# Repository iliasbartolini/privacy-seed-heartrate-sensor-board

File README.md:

# Privacy Seed - Heart rate sensor board

KiCAD custom heart rate board based on MAX30101 to connect to a [Arduino Nano shield](https://github.com/iliasbartolini/privacy-seed-heartrate-sensor-nano-shield).
This component is part of the [Privacy Seed](https://privacy-seed.org/) project.

## Schema

## PCB

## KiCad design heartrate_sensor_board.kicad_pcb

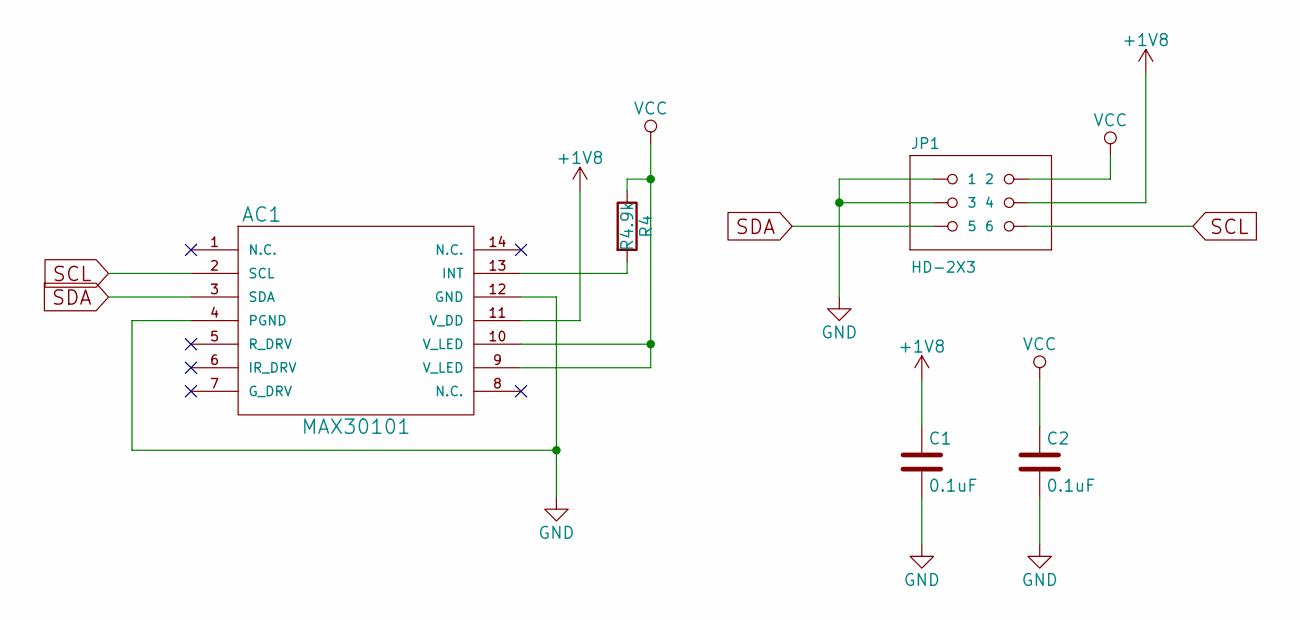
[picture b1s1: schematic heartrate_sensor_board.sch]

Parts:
AC1: MAX30101; fab-OESIP14
C1, C2: 0.1uF; fab-C1206FAB
JP1: HD-2X3; fab-2X03SMD-THROUGH
R4: R4.9k; fab-R1206FAB

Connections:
+1V8: AC1.11 (V_DD), C1.1, JP1.4
GND: AC1.4 (PGND), AC1.12 (GND), C1.2, C2.2, JP1.1, JP1.3
unnamed: AC1.13 (INT), R4.2
SCL: AC1.2 (SCL), JP1.6
SDA: AC1.3 (SDA), JP1.5
VCC: AC1.9 (V_LED), AC1.10 (V_LED), C2.1, JP1.2, R4.1

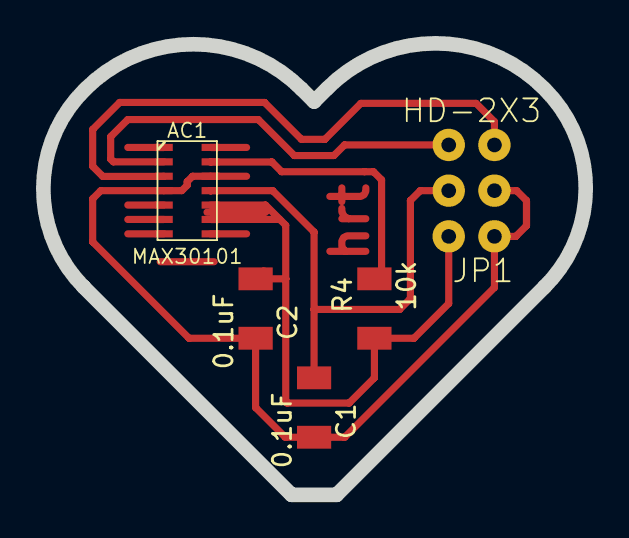
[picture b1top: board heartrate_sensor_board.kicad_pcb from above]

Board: 2 copper layers, 30.1 x 25.1 mm, 5 parts (0 on the bottom side), 6 nets.

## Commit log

2018-10-29 Added license and readme
2018-10-29 Try to fix images path
